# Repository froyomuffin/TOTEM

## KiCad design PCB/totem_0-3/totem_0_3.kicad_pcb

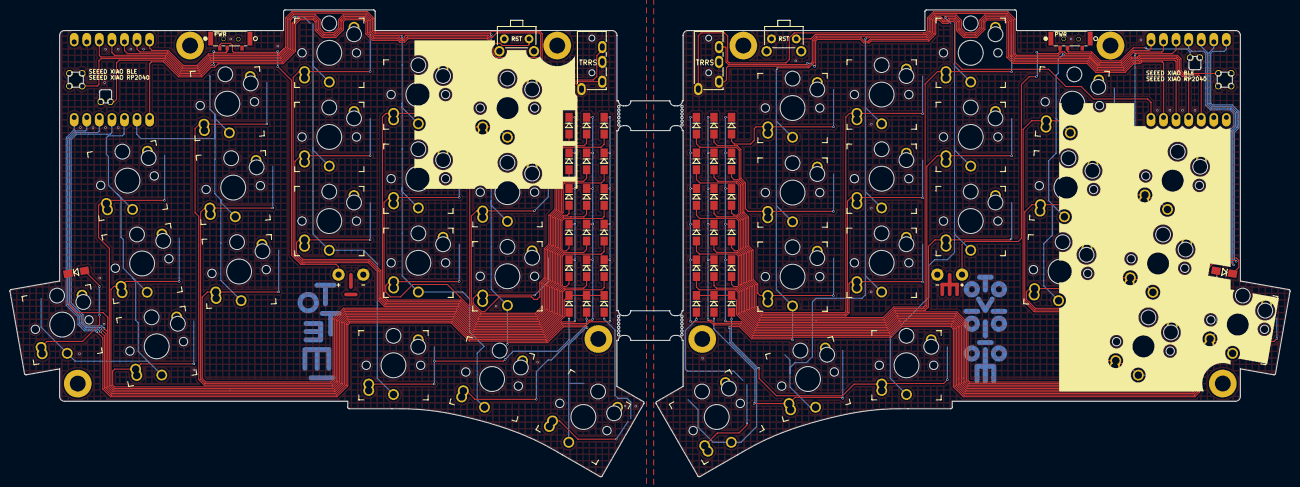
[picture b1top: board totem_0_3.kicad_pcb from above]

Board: 2 copper layers, 258.7 x 94.4 mm, 88 parts (0 on the bottom side), 70 nets.

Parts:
BAT+1, BAT+2: +; BatteryPad
BATGND1, BATGND2: -; BatteryPad
DL1, DL2, DL3, DL4, DL5, DL6, DL7, DL8, DL9, DL10, DL11, DL12, DL13, DL14, DL15, DL16, DL17, DL18, DL19: D_Small; Diode_SOD123
DR1, DR2, DR3, DR4, DR5, DR6, DR7, DR8, DR9, DR10, DR11, DR12, DR13, DR14, DR15, DR16, DR17, DR18, DR19: D_Small; Diode_SOD123
J1, J2: MJ-4PP-9; MJ-4PP-9_1side
PWR: SW_SPDT; MSK12C02
PWR#2: SW_SPDT; MSK12C02
RST: SW_Push; SKHLLCA010
RSW1: SW_Push; SKHLLCA010
SWL1, SWL2, SWL3, SWL4, SWL5, SWL6, SWL7, SWL8, SWL9, SWL10, SWL11, SWL12, SWL13, SWL14, SWL15, SWL16, SWL17, SWL18, SWL19: SW_Push_45deg; Kailh_socket_PG1353_optional
SWR1, SWR2, SWR3, SWR4, SWR5, SWR6, SWR7, SWR8, SWR9, SWR10, SWR11, SWR12, SWR13, SWR14, SWR15, SWR16, SWR17, SWR18, SWR19: SW_Push_45deg; Kailh_socket_PG1353_optional
U1, U2: xiao-ble; xiao-ble-smd-cutout

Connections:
BAT+_L: PWR.2 (B), U1.19 (BAT)
BAT+_R: PWR#2.2 (B), U2.19 (BAT)
COL0_L: SWL1.1, SWL6.1, SWL11.1, SWL16.1, U1.5 (A8_SDA/0.04_H)
COL0_R: SWR1.1, SWR6.1, SWR11.1, SWR16.1, U2.5 (A8_SDA/0.04_H)
COL1_L: SWL2.1, SWL7.1, SWL12.1, U1.6 (A9_SCL/0.05_H)
COL1_R: SWR2.1, SWR7.1, SWR12.1, U2.6 (A9_SCL/0.05_H)
COL2_L: SWL3.1, SWL8.1, SWL13.1, SWL17.1, U1.11 (A6_MOSI/1.15)
COL2_R: SWR3.1, SWR8.1, SWR13.1, SWR17.1, U2.11 (A6_MOSI/1.15)
COL3_L: SWL4.1, SWL9.1, SWL14.1, SWL18.1, U1.10 (A5_MISO/1.14)
COL3_R: SWR4.1, SWR9.1, SWR14.1, SWR18.1, U2.10 (A5_MISO/1.14)
COL4_L: SWL5.1, SWL10.1, SWL15.1, SWL19.1, U1.9 (A7_SCK/1.13)
COL4_R: SWR5.1, SWR10.1, SWR15.1, SWR19.1, U2.9 (A7_SCK/1.13)
GND_L: BATGND1.1, J1.C, RSW1.2, U1.13 (GND), U1.18 (GND), U1.20 (GND)
GND_R: BATGND2.1, J2.C, RST.2, U2.13 (GND), U2.18 (GND), U2.20 (GND)
unnamed: DL1.2 (A), SWL1.2
unnamed: DL2.2 (A), SWL2.2
unnamed: DL3.2 (A), SWL3.2
unnamed: DL4.2 (A), SWL4.2
unnamed: DL5.2 (A), SWL5.2
unnamed: DL6.2 (A), SWL6.2
unnamed: DL7.2 (A), SWL7.2
unnamed: DL8.2 (A), SWL8.2
unnamed: DL9.2 (A), SWL9.2
unnamed: DL10.2 (A), SWL10.2
unnamed: DL11.2 (A), SWL11.2
unnamed: DL12.2 (A), SWL12.2
unnamed: DL13.2 (A), SWL13.2
unnamed: DL14.2 (A), SWL14.2
unnamed: DL15.2 (A), SWL15.2
unnamed: DL16.2 (A), SWL16.2
unnamed: DL17.2 (A), SWL17.2
unnamed: DL18.2 (A), SWL18.2
unnamed: DL19.2 (A), SWL19.2
unnamed: DR1.2 (A), SWR1.2
unnamed: DR2.2 (A), SWR2.2
unnamed: DR3.2 (A), SWR3.2
unnamed: DR4.2 (A), SWR4.2
unnamed: DR5.2 (A), SWR5.2
unnamed: DR6.2 (A), SWR6.2
unnamed: DR7.2 (A), SWR7.2
unnamed: DR8.2 (A), SWR8.2
unnamed: DR9.2 (A), SWR9.2
unnamed: DR10.2 (A), SWR10.2
unnamed: DR11.2 (A), SWR11.2
unnamed: DR12.2 (A), SWR12.2
unnamed: DR13.2 (A), SWR13.2
unnamed: DR14.2 (A), SWR14.2
unnamed: DR15.2 (A), SWR15.2
unnamed: DR16.2 (A), SWR16.2
unnamed: DR17.2 (A), SWR17.2
unnamed: DR18.2 (A), SWR18.2
unnamed: DR19.2 (A), SWR19.2
RESET_L: RSW1.1, U1.17 (RESET)
RESET_R: RST.1, U2.17 (RESET)
ROW0_L: DL1.1 (K), DL2.1 (K), DL3.1 (K), DL4.1 (K), DL5.1 (K), U1.1 (A2/0.02_H)
ROW0_R: DR1.1 (K), DR2.1 (K), DR3.1 (K), DR4.1 (K), DR5.1 (K), U2.1 (A2/0.02_H)
ROW1_L: DL6.1 (K), DL7.1 (K), DL8.1 (K), DL9.1 (K), DL10.1 (K), U1.2 (A4/0.03_H)
ROW1_R: DR6.1 (K), DR7.1 (K), DR8.1 (K), DR9.1 (K), DR10.1 (K), U2.2 (A4/0.03_H)
ROW2_L: DL11.1 (K), DL12.1 (K), DL13.1 (K), DL14.1 (K), DL15.1 (K), U1.3 (A10/0.28)
ROW2_R: DR11.1 (K), DR12.1 (K), DR13.1 (K), DR14.1 (K), DR15.1 (K), U2.3 (A10/0.28)
ROW3_L: DL16.1 (K), DL17.1 (K), DL18.1 (K), DL19.1 (K), U1.4 (A11/0.29)
ROW3_R: DR16.1 (K), DR17.1 (K), DR18.1 (K), DR19.1 (K), U2.4 (A11/0.29)
RX_L: J1.B, U1.8 (B9_RX/1.12)
RX_R: J2.B, U2.8 (B9_RX/1.12)
TX_L: J1.A, U1.7 (B8_TX/1.11)
TX_R: J2.A, U2.7 (B8_TX/1.11)
VBAT_L: BAT+1.1, PWR.3 (C)
VBAT_R: BAT+2.1, PWR#2.3 (C)
VCC_L: J1.D, U1.12 (3V3)
VCC_R: J2.D, U2.12 (3V3)

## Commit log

2024-08-19 Upgrade kicad version
2024-08-19 Add template PG1353
2024-08-19 Switch in PG1353 and reroute some traces for SWL16
2024-08-19 Move GND_R in SWR16
2024-08-19 Fix a bunch of traces on FR
2024-08-19 Fix ground in SWR6
2024-08-19 Fix a bunch of traces on FL
2024-08-19 Switch PG1353 third pin to socket
2024-08-19 Switch to updated PG1353
2024-08-19 Fix a few things to handle socket pin update
2024-08-19 Clean up some connection
2024-08-19 Upgrade schematic kicad version
2024-08-19 Fix a bunch of traces in F
2024-08-19 Fix a bunch of traces on B
2024-08-19 Fix two traces on F
2024-08-19 Fix some cut traces
2024-08-19 Cleanups
2024-08-19 Switch the mounting pins on 1353 to NPTH
2024-08-19 Use updated 1353
2024-08-19 Move tight trace
2024-08-21 Cleanup
2024-08-28 Remove hidden trace
2024-08-29 Update revision
2024-09-01 Expand socket slots to 1.5mm for 3305 millmax
2024-09-01 Adjust traces for new holes
2024-09-02 DRC refill
2026-03-16 Add modified case
2026-03-16 Added modified liminal chimeras caps to match
